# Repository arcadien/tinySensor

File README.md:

# TinySensor 

TinySensor aims to provide a customisable firmware and a hardware design for low-power environment sensors using wireless communication.

In the complete system, data is processed by a [Domoticz](https://domoticz.com/)/[RFlink](http://www.rflink.nl/blog2/) couple.
Data decoding is also tested using [RTL_433](https://github.com/merbanan/rtl_433) decoder.
Large part of the code, especially wireless encoders, are unit-tested.

| TinySensor v3.0 board (cuttable) | Mushroom casing | Wall box | tinyDecoders receiver |
|:---:|:---:|:---:|:---:|
|  |  |  |  |

*TinySensor v3.0 schematic (click to enlarge; [PDF with title block](hardware/tinysensor/tinysensor_schematic.pdf)). The board can be cut along the dotted line at x = 147 to drop the CR2032 area, as in the mushroom.*

## Supported MCUs
* ATTiny84a

## Supported sensors
* I2C sensors (eg. [Bosch BME/BMP280](https://www.bosch-sensortec.com/bst/products/all_products/bme280))
* Analog sensors (eg. [LM35](http://www.ti.com/lit/ds/symlink/lm35.pdf))
* OneWire sensors (eg. [Dallas DS18S20](https://datasheets.maximintegrated.com/en/ds/DS18S20.pdf))
* Luminosity sensor ([ROHM BH1750](https://www.mouser.com/datasheet/2/348/bh1750fvi-e-186247.pdf), I2C)

## Wireless technology
* "one pin" emitters. Tested with low-cost 433 MHz emitters.

## Wireless protocols
* Environment frame (temperature, humidity, pressure): Oregon Scientific v2.1 (class `OregonV3`) **or** Lacrosse WS7000, at most one per build. A build without either sends no environment frame.
* Luminosity: always a dedicated Lacrosse WS7000 frame (Oregon has no light frame), so `LACROSSE_ID` is required whenever the BH1750 is fitted.
* Battery level and analog input: optional X10 RFXmeter frames, not sent when the battery is low.

## Used libraries
Various libraries are used here, and some where tweaked to remove any Arduino dependencies, making the whole firmware more compact:
* Sparkfun [BME280 sensor library](https://github.com/sparkfun/SparkFun_BME280_Arduino_Library) with all SPI related code removed
* [Tiny I2C](https://github.com/arcadien/tiny-i2c.git) of [David Johnson-Davies](https://github.com/technoblogy)
* [Unity test harness](http://www.throwtheswitch.org/unity) from Throw The Switch, for all testing code
* DS18B20 library of [Jacek Wieczorek](https://github.com/Jacajack/avr-ds18b20)

## Useful documentation about low power AVR
* [AVR4013: picoPower Basics](http://www.microchip.com/downloads/en/AppNotes/doc8349.pdf)

## Development

The firmware is built with [PlatformIO](https://platformio.org/) and configured entirely at build time: each physical sensor is one PlatformIO environment (`S_02`…`S_05`, `robot`, `devmodule`, `SOLAR_TEST`, `mushroom`) whose `build_flags` select protocol, sensors and calibration. See [docs/environments.md](docs/environments.md) to calibrate or add a board.

```bash
pio test -d emitter -e native_debug        # encoder and library unit tests, on the host
pio test -d emitter -e native_cycle_oregon # one measurement cycle (runCycle) per build variant;
                                           # also native_cycle_oregon_vcc, _oregon_divider,
                                           # _lacrosse, _x10
pio run -d emitter -e S_02                 # firmware for one board
pio run -d emitter -e S_02 -t upload       # flash it
```

> **Flashing with a BME280 plugged in.** ISP and I2C share the ATtiny84A pins PA4 (SCK / SCL) and PA6 (MOSI / SDA). On **v3.0**, R9 and R10 (330 Ω) sit in series between the MCU and the sensor connectors J3/J14, so the programmer drives SCK and MOSI without the sensor holding them: the board should flash with the BME280 in place (not yet checked on a built board). On **v2.2 and earlier**, unplug the BME280 before flashing, otherwise flashing fails; always wire it through its JST connector, never solder it to the board.

CI runs the native tests (`native_debug` and every `native_cycle_*`), compile-fail checks for invalid flag combinations (`emitter/test/compile_fail/`), sensor-variant checks (`emitter/test/build_variants/`), `clang-format` and a build of every board (including `mushroom`).

* Architecture: [docs/architecture.md](docs/architecture.md)
* Step debugging over debugWIRE: [docs/debugging.md](docs/debugging.md)
* Requirements: see [Requirement-based development](#requirement-based-development) below

## Requirement-based development

This project follows requirement-based development (RBD): every behaviour of the firmware, the receiver and the boards is written down as a requirement before it is tested and coded. Each requirement, its tests and the commits that implement it can therefore be traced to each other.

The cycle for each change:

1. **Requirement.** The change is first written as a requirement with an ID such as `FUNC-OREGON-001` (category, domain, number), a status (`validated` or `draft`) and its dependencies.
2. **Tests.** Tests are written next. Each Unity test function carries the ID it verifies on the line above it: `// @req FUNC-OREGON-001`. Requirements that no host test can observe (AVR registers, wiring, bench measurements) say instead how they are verified: by inspection, by a build, or on the bench.
3. **Code.** The code then makes the tests pass. The linter (`clang-format` 18.1.8) and the full native test suite must pass before each commit.
4. **Commit.** Each commit names what it serves: `req(ID):`, `test(ID):`, `feat(ID):`, `tech(ID):`, `perf(ID):`, `ui(ID):`, `conf(ID):` or `arch(ID):`; `plan:` for workflow files; `hw:`, `docs:`, `fix:`, `chore:`, `style:` or `refactor:` outside the code cycle (`hw:` is added in `.rbd/config.yml`, `extra_commit_prefixes`). The rbd plugin's pre-push hook rejects any other prefix, and a code commit whose ID is missing or not `validated`.

`git log --grep FUNC-MAIN-001` and `grep -rn FUNC-MAIN-001 emitter/test` show where a requirement was written, tested and implemented.

| Document | Contents |
|---|---|
| [requirements/functional.md](requirements/functional.md) | `FUNC`: observable behaviour: radio frames, measurements, battery, receiver decoding, RFLink lines |
| [requirements/ui.md](requirements/ui.md) | `UI`: what the receiver OLED shows |
| [requirements/configuration.md](requirements/configuration.md) | `CONF`: build flags, PlatformIO environments, CI |
| [requirements/platform.md](requirements/platform.md) | `PLAT`: hardware use: pins, registers, timers, sleep, board pull-ups |
| [requirements/technical.md](requirements/technical.md) | `TECH`: classes, interfaces, memory layout, test doubles |
| [requirements/performance.md](requirements/performance.md) | `PERF`: none yet |
| [docs/architecture.md](docs/architecture.md) | Component diagram, dependency injection map, and a requirement → component traceability table |
| [audits/](audits/) | Audit and review reports. Each one starts with the commit it audited, so `git diff <hash>..HEAD` shows what changed since |
| [audits/exclusions.yml](audits/exclusions.yml) | Audit findings accepted on purpose, with their justification |
| [.rbd/config.yml](.rbd/config.yml) | ID format, test tag convention and linter command |

Non-technical requirements (`FUNC`, `UI`, `CONF`, `PLAT`) describe what can be observed, without class or function names. Those details live in `TECH`. Requirement IDs cited in these documents link to their heading. The workflow is driven by the [`rbd` Claude Code plugin](https://github.com/arcadien/claude-marketplace/tree/main/plugins/rbd) (`/rbd`, `/rbd-audit`, `/rbd-review`); see `CLAUDE.md`.

## Hardware and enclosure

* KiCad board (v3.0) in `hardware/tinysensor/`: [schematic (PDF)](hardware/tinysensor/tinysensor_schematic.pdf), regenerated with `kicad-cli sch export pdf -o hardware/tinysensor/tinysensor_schematic.pdf hardware/tinysensor/tinysensor.kicad_sch`; with its [backlog](hardware/tinysensor/BACKLOG.md) and a [rework guide for v2.2 boards](hardware/tinysensor/REWORK_v2.2.md).
* OpenSCAD enclosures (wall box, radiation shield, mushroom, receiver) in `enclosing/`, see [enclosing/README.md](enclosing/README.md).
* Header renders: `kicad-cli pcb render --rotate '-45,0,45' --quality high --width 1400 --height 800 --zoom 1.22 -o docs/img/tinysensor_v3_iso.png hardware/tinysensor/tinysensor.kicad_pcb` and, from `enclosing/receiver/`, `openscad --preview -D 'part="assembly"' --camera=0,0,0,55,0,25,0 --viewall --autocenter --projection=o --imgsize=1400,1000 -o ../../docs/img/receiver_iso.png receiver.scad`; from `enclosing/basic/`, `openscad --preview -D 'part="exploded"' --camera=0,0,0,55,0,25,0 --viewall --autocenter --projection=o --imgsize=1400,1000 -o ../../docs/img/wallbox_exploded_iso.png tinysensor_box.scad`. Schematic image: `kicad-cli sch export svg --exclude-drawing-sheet -o <dir> hardware/tinysensor/tinysensor.kicad_sch`, then a white background rectangle is added so it stays readable in dark mode.

## Hardware options

TinySensor can use combination of sensors, the limit comes from amount of flash memory on the ATTiny.

### DS18B20

OneWire sensor, cheap and efficient.

### BMP/BME 280 environment sensor
The [BMP280](https://www.bosch-sensortec.com/products/environmental-sensors/pressure-sensors/pressure-sensors-bmp280-1.html) and the [BME280](https://www.bosch-sensortec.com/products/environmental-sensors/humidity-sensors-bme280/) share the same library, but the BME provide humidity sensing, and thus use more memory.

### Analog sensor

Analog sensor can be used for [LM35](https://www.ti.com/lit/ds/symlink/lm35.pdf) temperature sensor, or [LDR](https://en.wikipedia.org/wiki/Photoresistor).

### LM35 temperature sensor

On v2.2 and v3.0 boards running from 2×AA/AAA, the LM35 can be powered by an off-board 5 V boost module switched on PB2 only during measurements (`USE_SWITCHED_5V`), see [VARIANTE_LM35.md](hardware/tinysensor/VARIANTE_LM35.md). The instructions below are for v2.1.

#### Without negative temperature support
A 0v ground reference is needed.
Solder pads *2* and *3* of **J4**, (rear side) as well **JP3**. 

#### With negative temperature support
In the case of a *-CAZ* version, temperature below 0 can be measured. 
To allow this, two 1N914 diodes must be placed to put the sensor reference below 0v. This setup is documented in the LM35 datasheet.
On TinySensor board v2.1 and up, this can be implemented by:
* solding **D2** and **D3** diodes
* solding **R4** with a value of 18k
* solding **JP3** to bypass C3 capacitor
* solding pads *1* and *2* of **J4** (rear side) to set ground reference.

#### Notes about swing

You can add a filter capacitor *C3* to avoid swing if the wire is long. In this case, do not solder *JP3*.
See datasheet for details.

### LDR
Use the right value for **R4** (should match the used LDR) and solder **JP3** and, on **JP4**, middle and *3* pads. This way, there will be no RC filter (no cap because of **J3**) and Vss analog reference thanks of **JP4**.

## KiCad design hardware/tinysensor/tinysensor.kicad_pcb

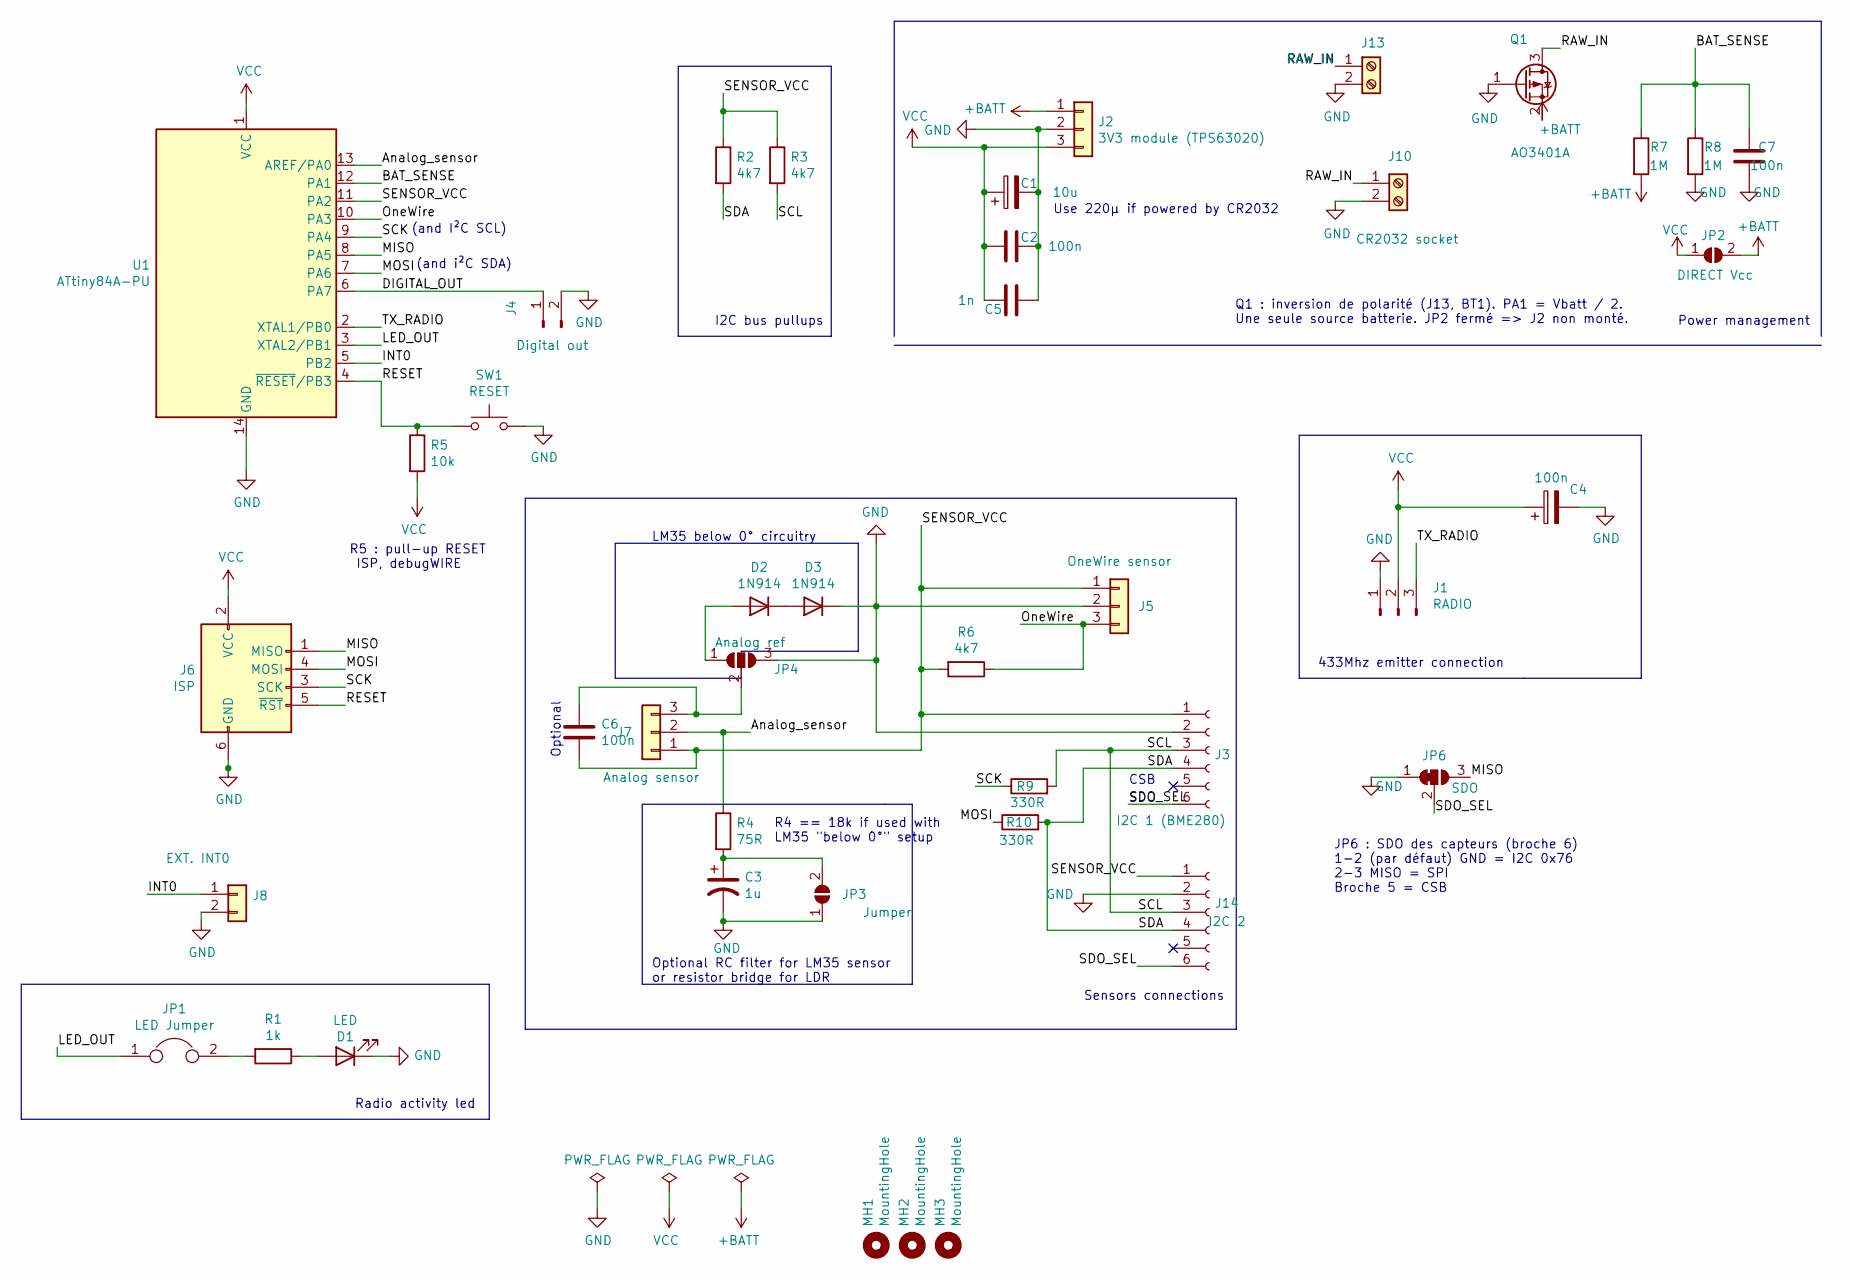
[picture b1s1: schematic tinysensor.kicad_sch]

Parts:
C1: 10u; CP_Radial_D6.3mm_P2.50mm
C2, C7: 100n; C_Rect_L7.0mm_W2.0mm_P5.00mm
C3: 1u; CP_Radial_D4.0mm_P1.50mm
C4, C6: 100n; C_Disc_D3.0mm_W1.6mm_P2.50mm
C5: 1n; C_Disc_D3.0mm_W1.6mm_P2.50mm
D1: LED; LED_D5.0mm
D2, D3: 1N914; D_DO-35_SOD27_P7.62mm_Horizontal
J1: RADIO; PinHeader_1x03_P2.54mm_Vertical
J2: 3V3 module (TPS63020); PinHeader_1x03_P2.54mm_Vertical
J3: I2C 1 (BME280); JST_EH_B6B-EH-A_1x06_P2.50mm_Vertical
J4: Digital out; PinHeader_1x02_P2.54mm_Vertical
J5: OneWire sensor; PinHeader_1x03_P2.54mm_Vertical
J6: ISP; ICSP_SOCKET_MINI_2x3
J7: Analog sensor; PinHeader_1x03_P2.54mm_Vertical
J8: EXT. INT0; PinHeader_1x02_P2.54mm_Vertical
J10: CR2032 socket; BatteryHolder_Keystone_1060_1x2032
J13: RAW IN; JST_XH_B2B-XH-A_1x02_P2.50mm_Vertical
J14: I2C 2; JST_EH_B6B-EH-A_1x06_P2.50mm_Vertical
JP1: LED Jumper; PinHeader_1x02_P2.54mm_Vertical
JP2: DIRECT Vcc; SolderJumper-2_P1.3mm_Open_TrianglePad1.0x1.5mm
JP3: Jumper; SolderJumper-2_P1.3mm_Open_TrianglePad1.0x1.5mm
JP4: Analog ref; SolderJumper-3_P1.3mm_Open_Pad1.0x1.5mm_NumberLabels
JP6: SDO; SolderJumper-3_P1.3mm_Open_Pad1.0x1.5mm_NumberLabels
MH1, MH2, MH3: MountingHole; MountingHole_3.2mm_M3
Q1: AO3401A; SOT-23
R1: 1k; R_Axial_DIN0204_L3.6mm_D1.6mm_P1.90mm_Vertical
R2, R3, R6: 4k7; R_Axial_DIN0204_L3.6mm_D1.6mm_P7.62mm_Horizontal
R4: 75R; R_Axial_DIN0204_L3.6mm_D1.6mm_P7.62mm_Horizontal
R5: 10k; R_Axial_DIN0204_L3.6mm_D1.6mm_P1.90mm_Vertical
R7, R8: 1M; R_Axial_DIN0204_L3.6mm_D1.6mm_P1.90mm_Vertical
R9, R10: 330R; R_Axial_DIN0204_L3.6mm_D1.6mm_P1.90mm_Vertical
SW1: RESET; SW_PUSH_6mm_H4.3mm
U1: ATtiny84A-PU; DIP-14_W7.62mm

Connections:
+BATT: J2.1, JP2.2 (B), Q1.2 (S), R7.2
/Analog_sensor: J7.2, R4.1, U1.13 (AREF/PA0)
/BAT_SENSE: C7.1, R7.1, R8.1, U1.12 (PA1)
/DIGITAL_OUT: J4.1, U1.6 (PA7)
/INT0: J8.1, U1.5 (PB2)
/LED_OUT: JP1.1, U1.3 (XTAL2/PB1)
/MISO: J6.1 (MISO), JP6.3 (B), U1.8 (PA5)
/MOSI: J6.4 (MOSI), R10.1, U1.7 (PA6)
/OneWire: J5.3, R6.1, U1.10 (PA3)
/RAW_IN: J10.1, J13.1, Q1.3 (D)
/RESET: J6.5 (~RST), R5.1, SW1.1, U1.4 (~RESET/PB3)
/SCK: J6.3 (SCK), R9.1, U1.9 (PA4)
/SCL: J3.3, J14.3, R3.2, R9.2
/SDA: J3.4, J14.4, R2.2, R10.2
/SDO_SEL: J3.6, J14.6, JP6.2 (C)
/SENSOR_VCC: C6.1, J3.1, J5.1, J7.1, J14.1, R2.1, R3.1, R6.2, U1.11 (PA2)
/TX_RADIO: J1.3, U1.2 (XTAL1/PB0)
GND: C1.2, C2.1, C3.2, C4.2, C5.2, C7.2, D1.1 (K), D3.1 (K), J1.1, J2.2, J3.2, J4.2, J5.2, J6.6 (GND), J8.2, J10.2, J13.2, J14.2, JP3.1 (A), JP4.3 (B), JP6.1 (A), Q1.1 (G), R8.2, SW1.2, U1.14 (GND)
unnamed: D1.2 (A), R1.1
unnamed: D2.2 (A), JP4.1 (A)
unnamed: D2.1 (K), D3.2 (A)
unnamed: C6.2, J7.3, JP4.2 (C)
unnamed: JP1.2, R1.2
unnamed: C3.1, JP3.2 (B), R4.2
VCC: C1.1, C2.2, C4.1, C5.1, J1.2, J2.3, J6.2 (VCC), JP2.1 (A), R5.2, U1.1 (VCC)

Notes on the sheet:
CSB
Radio activity led
Power management
Optional RC filter for LM35 sensor or resistor bridge for LDR
(and I²C SCL)
Q1 : inversion de polarité (J13, BT1). PA1 = Vbatt / 2. Une seule source batterie. JP2 fermé => J2 non monté.
SDO
Use 220µ if powered by CR2032
JP6 : SDO des capteurs (broche 6) 1-2 (par défaut) GND = I2C 0x76 2-3 MISO = SPI Broche 5 = CSB
R5 : pull-up RESET ISP, debugWIRE
Sensors connections
LM35 below 0° circuitry
I2C bus pullups
(and i²C SDA)
Optional
R4 == 18k if used with LM35 "below 0°" setup
433Mhz emitter connection

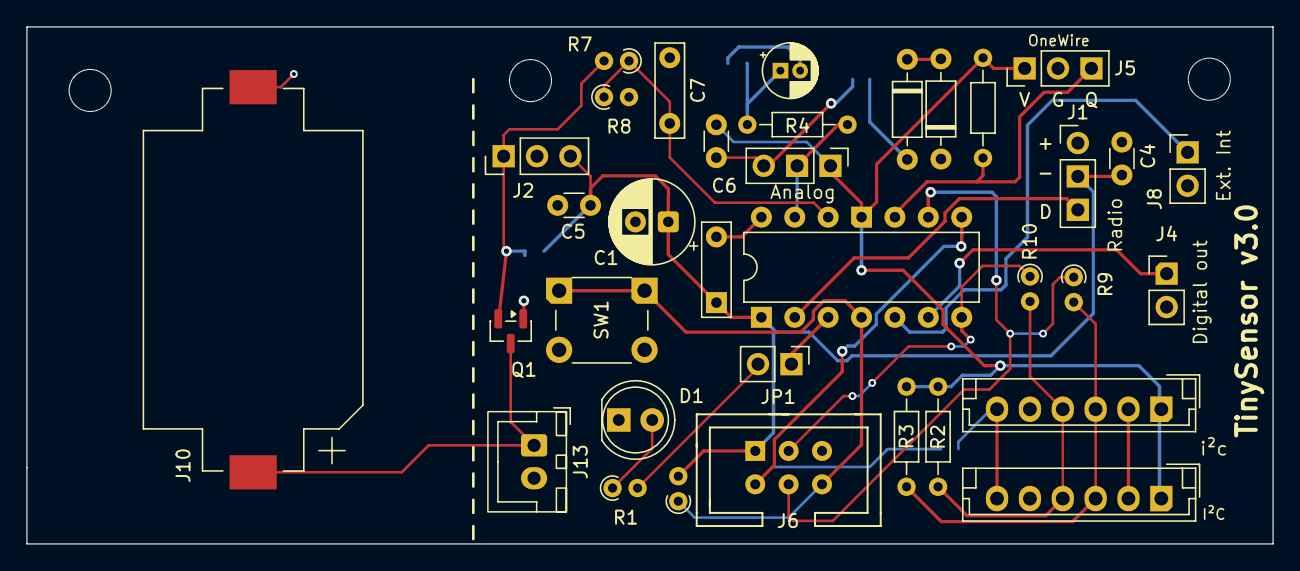
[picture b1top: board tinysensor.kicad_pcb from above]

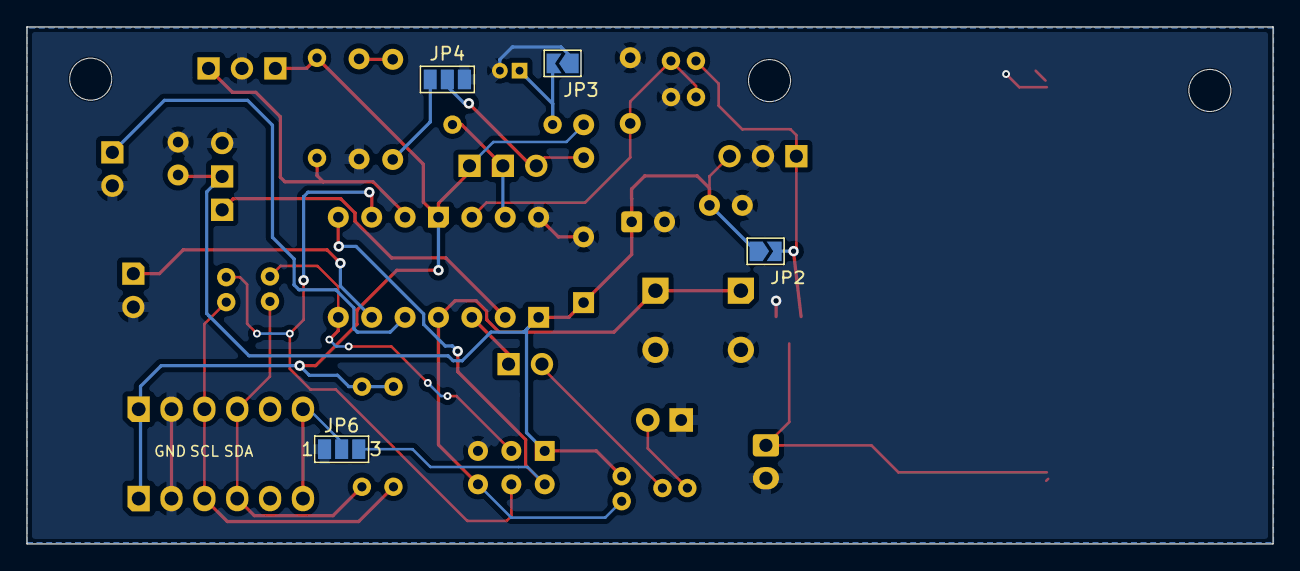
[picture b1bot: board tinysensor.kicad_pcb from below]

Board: 2 copper layers, 94.8 x 39.3 mm, 42 parts (4 on the bottom side), 25 nets.

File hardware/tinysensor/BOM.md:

# tinySensor board: bill of materials (v3.0)

Generated from the v3.0 schematic (`tinysensor.kicad_sch`, rev 3.0), grouped by value and footprint. No part is marked DNP: which connectors and modules to fit depends on the sensor unit, see [`WIRING.md`](WIRING.md) and [`docs/environments.md`](../../docs/environments.md). v2.2 boards: see [`REWORK_v2.2.md`](REWORK_v2.2.md).

Regenerate after a schematic change:

```bash
kicad-cli sch export bom --fields 'Reference,Value,Footprint,${QUANTITY}' \
  --labels 'Refs,Value,Footprint,Qty' --group-by 'Value,Footprint' --ref-range-delimiter '' \
  -o bom.csv tinysensor.kicad_sch
```

## Components

| Refs | Qty | Value | Package |
|---|:-:|---|---|
| U1 | 1 | ATtiny84A-PU | DIP-14 |
| Q1 | 1 | AO3401A (P-MOSFET) | SOT-23 |
| D1 | 1 | LED | 5 mm THT |
| D2, D3 | 2 | 1N914 | DO-35 |
| C1 | 1 | electrolytic, value per supply: 10 µF (2×AA/AAA, or 18650 through the TPS63020), 220 µF **low-leakage** (CR2032) | radial Ø6.3, 2.5 mm pitch |
| C3 | 1 | 1 µF electrolytic | radial Ø4, 1.5 mm pitch |
| C2 | 1 | 100 nF film (global decoupling) | 7 × 2 mm, 5 mm pitch |
| C7 | 1 | 100 nF film (PA1 battery divider; no tantalum: its leakage would bias the 500 kΩ divider) | 7 × 2 mm, 5 mm pitch |
| C4 | 1 | 100 nF ceramic (radio, next to J1) | disc Ø3, 2.5 mm pitch |
| C6 | 1 | 100 nF ceramic | disc Ø3, 2.5 mm pitch |
| C5 | 1 | 1 nF ceramic | disc Ø3, 2.5 mm pitch |
| R1 | 1 | 1 kΩ | axial DIN0204, vertical, 1.9 mm pitch |
| R2, R3, R6 | 3 | 4.7 kΩ | axial DIN0204, 7.62 mm pitch |
| R4 | 1 | 75 Ω | axial DIN0204, 7.62 mm pitch |
| R5 | 1 | 10 kΩ (RESET pull-up) | axial DIN0204, vertical, 1.9 mm pitch |
| R7, R8 | 2 | 1 MΩ (PA1 battery divider) | axial DIN0204, vertical, 1.9 mm pitch |
| R9, R10 | 2 | 330 Ω (SCL / SDA series, ISP isolation) | axial DIN0204, vertical, 1.9 mm pitch |
| SW1 | 1 | RESET push button | 6 mm THT, H 4.3 mm |

## Connectors and holders

| Refs | Qty | Function | Part |
|---|:-:|---|---|
| J1 | 1 | RADIO (433 MHz emitter) | 1×3 pin header, 2.54 mm |
| J2 | 1 | 3V3 module (TPS63020) | 1×3 pin header, 2.54 mm |
| J5 | 1 | OneWire sensor | 1×3 pin header, 2.54 mm |
| J7 | 1 | Analog sensor | 1×3 pin header, 2.54 mm |
| J4 | 1 | Digital out | 1×2 pin header, 2.54 mm |
| J8 | 1 | EXT. INT0 | 1×2 pin header, 2.54 mm |
| JP1 | 1 | LED jumper | 1×2 pin header, 2.54 mm + jumper cap |
| J3 | 1 | I2C 1 (BME280) | JST-EH 6-pin vertical, B6B-EH-A |
| J14 | 1 | I2C 2 | JST-EH 6-pin vertical, B6B-EH-A |
| J6 | 1 | ISP | 2×3 mini ICSP socket (project library) |
| J13 | 1 | RAW IN | JST-XH 2-pin vertical, B2B-XH-A |
| J10 | 1 | CR2032 socket | Keystone 1060 |

## No part to buy

| Refs | Function |
|---|---|
| JP2 | DIRECT Vcc solder jumper (2 pads, open) |
| JP3 | solder jumper (2 pads, open) |
| JP4 | Analog ref solder jumper (3 pads, open) |
| JP6 | BME280 SDO solder jumper (3 pads, open: bridge 1–2 for I2C at 0x76, the firmware address, or 2–3 for SPI; choose at assembly) |
| MH1–MH3 | M3 mounting holes |

## Off-board modules (not on the schematic)

Fitted per sensor unit, wiring in [`WIRING.md`](WIRING.md): 433 MHz OOK emitter on J1, BME280 or BMP280 breakout on J3, TPS63020 3.3 V buck-boost module on J2, DS18B20 on J5, LM35 variant on J7 ([`VARIANTE_LM35.md`](VARIANTE_LM35.md)), CR2032 in J10, or 2×AA/AAA or an 18650 (through a TP4056) on J13: the board has no 18650 holder.

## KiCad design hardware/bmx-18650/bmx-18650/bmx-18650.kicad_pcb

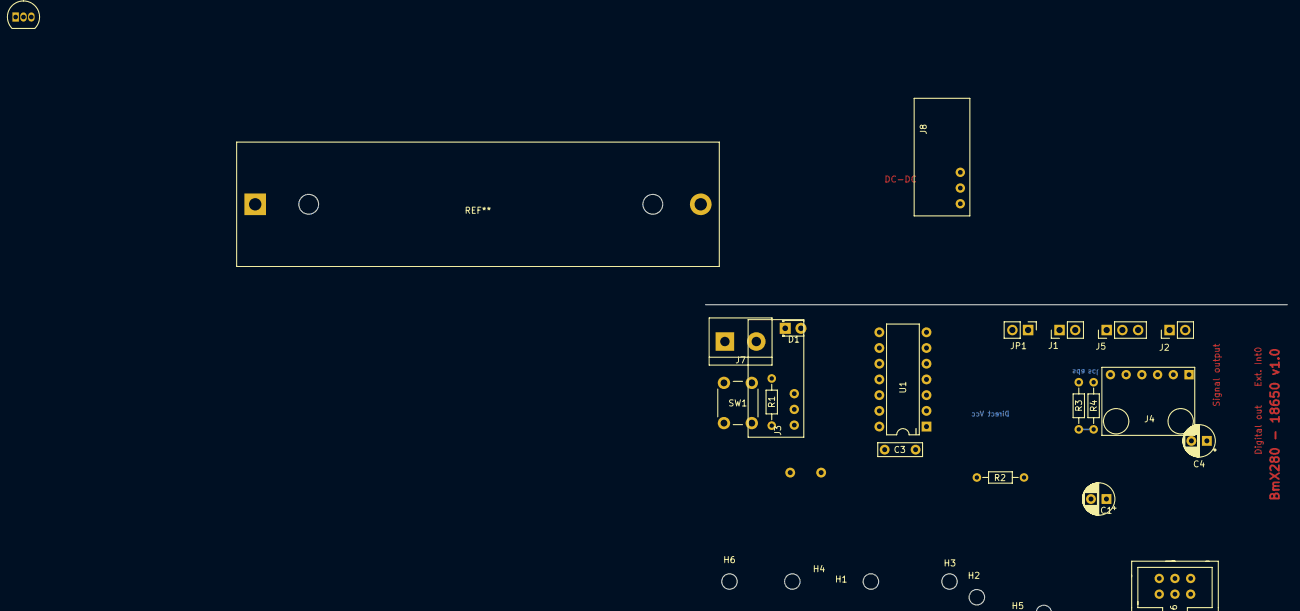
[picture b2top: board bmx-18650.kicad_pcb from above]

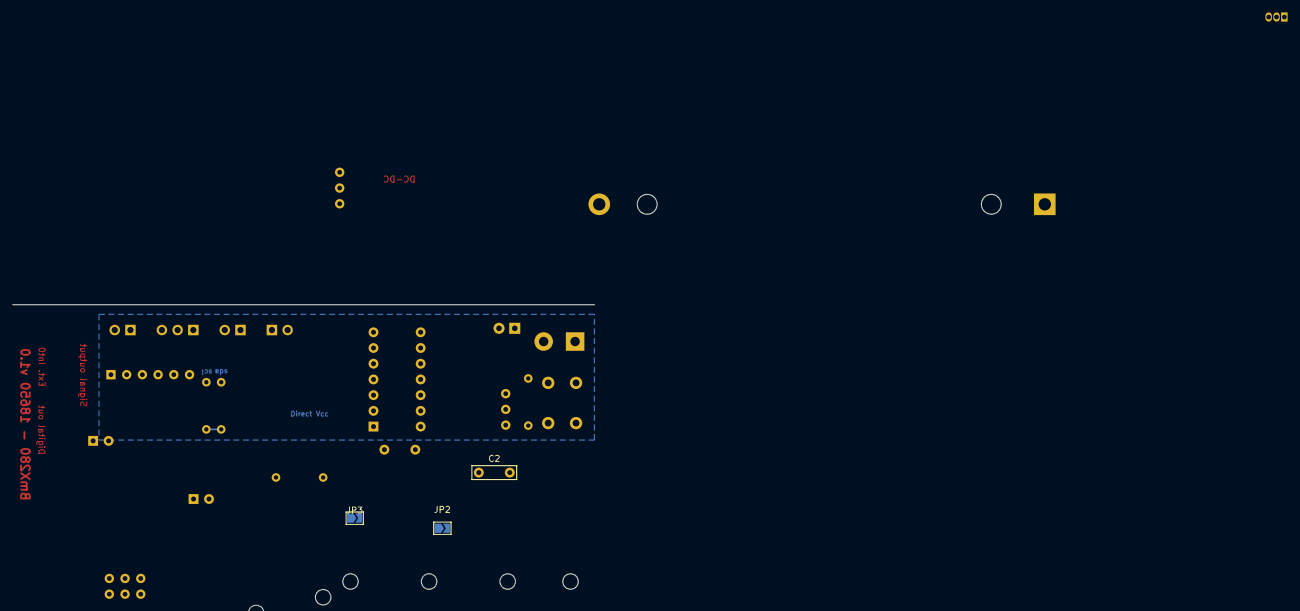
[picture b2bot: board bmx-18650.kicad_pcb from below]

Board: 2 copper layers, 29 parts (3 on the bottom side), 17 nets.

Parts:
C1, C4: 10u; CP_Radial_D5.0mm_P2.50mm
C2, C3: 100n; C_Rect_L7.0mm_W2.0mm_P5.00mm
D1: LED; LED_D1.8mm_W3.3mm_H2.4mm
H1, H2, H3, H4, H5, H6: MountingHole; MountingHole_2.5mm
J1: Ext. interrupt; PinHeader_1x02_P2.54mm_Vertical
J2: Digital out; PinHeader_1x02_P2.54mm_Vertical
J3: VCC charge pump; DC-DC_0.9v-3.3v_to_3.3v
J4: BMx280 socket; BMx280_breakout
J5: Radio emitter; PinHeader_1x03_P2.54mm_Vertical
J6: ISP; ICSP_SOCKET_MINI_2x3
J7: Terminal; TerminalBlock_bornier-2_P5.08mm
J8: RF charge pump; DC-DC_0.9v-3.3v_to_3.3v
JP1: LED Jumper; PinHeader_1x02_P2.54mm_Vertical
JP2, JP3: Bypass; SolderJumper-2_P1.3mm_Open_TrianglePad1.0x1.5mm
Q1: BS170; TO-92_Inline
R1, R3, R4: R; R_Axial_DIN0204_L3.6mm_D1.6mm_P7.62mm_Horizontal
R2: 10k; R_Axial_DIN0204_L3.6mm_D1.6mm_P7.62mm_Horizontal
SW1: SW_Push; SW_PUSH_6mm_H4.3mm
U1: ATtiny84A-PU; DIP-14_W7.62mm

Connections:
+BATT: J3.1, J7.1, J8.3, JP2.2 (B), JP3.1 (A), U1.12 (PA1)
/DIGITAL_OUT: J2.1, U1.6 (PA7)
/INT0: J1.1, U1.5 (PB2)
/LED_OUT: JP1.1, U1.3 (XTAL2/PB1)
/MISO: J6.1 (MISO), U1.8 (PA5)
/RESET: J6.5 (~RST), R2.1, SW1.1, U1.4 (~RESET/PB3)
/SCL: J4.3, J6.3 (SCK), R4.2, U1.9 (PA4)
/SDA: J4.4, J6.4 (MOSI), R3.2, U1.7 (PA6)
/SENSOR_VCC: J4.1, Q1.2 (G), R3.1, R4.1, U1.11 (PA2)
/TX_RADIO: J5.3, U1.2 (XTAL1/PB0)
GND: C1.2, C2.2, C3.1, C4.2, D1.2 (A), J1.2, J2.2, J3.2, J4.2, J4.6, J5.1, J6.6 (GND), J7.2, Q1.3 (S), SW1.2, U1.14 (GND)
unnamed: D1.1 (K), R1.1
unnamed: J8.2, Q1.1 (D)
unnamed: JP1.2, R1.2
unnamed: C2.1, U1.13 (AREF/PA0)
VCC: C1.1, C3.2, J3.3, J6.2 (VCC), JP2.1 (A), R2.2, U1.1 (VCC)
VDD: C4.1, J5.2, J8.1, JP3.2 (B)

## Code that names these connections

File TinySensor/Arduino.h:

/*
  pins_arduino.h - Pin definition functions for Arduino
  Part of Arduino - http://www.arduino.cc/

  Copyright (c) 2007 David A. Mellis
  Copyright (c) 2015~2020 Spence Konde

  This library is free software; you can redistribute it and/or
  modify it under the terms of the GNU Lesser General Public
  License as published by the Free Software Foundation; either
  version 2.1 of the License, or (at your option) any later version.

  This library is distributed in the hope that it will be useful,
  but WITHOUT ANY WARRANTY; without even the implied warranty of
  MERCHANTABILITY or FITNESS FOR A PARTICULAR PURPOSE.  See the GNU
  Lesser General Public License for more details.

  You should have received a copy of the GNU Lesser General
  Public License along with this library; if not, write to the
  Free Software Foundation, Inc., 59 Temple Place, Suite 330,
  Boston, MA  02111-1307  USA

  $Id: wiring.h 249 2007-02-03 16:52:51Z mellis $
*/

#ifndef Pins_Arduino_h
#define Pins_Arduino_h

#define ATTINYX4 1
#define __AVR_ATtinyX4__
#define USE_SOFTWARE_SPI 1

#include <avr/pgmspace.h>

#define NUM_DIGITAL_PINS            12
#define NUM_ANALOG_INPUTS           8

#define analogInputToDigitalPin(p)  (p)

#define digitalPinHasPWM(p)         ((p) == 5 || (p) == 6 || (p) == 7 || (p) == 8)

//This part has a USI, not an SPI module. Accordingly, there is no MISO/MOSI in hardware. There's a DI and a DO. When the chip is used as master, DI is used as MISO, DO is MOSI; the defines here specify the pins for master mode, as SPI master is much more commonly used in Arduino-land than SPI slave, and these defines are required for compatibility. Be aware of this when using the USI SPI fucntionality (and also, be aware that the MISO and MOSI markings on the pinout diagram in the datasheet are for ISP programming, where the chip is a slave. The pinout diagram included with this core attempts to clarify this)

#define ADC_TEMPERATURE 34

#define SS   3
#define MOSI 5
#define MISO 6
#define SCK  4


#define USI_DDR_PORT DDRA
#define USI_SCK_PORT DDRA
#define USCK_DD_PIN DDA4
#define DO_DD_PIN DDA5
#define DI_DD_PIN DDA6
#  define DDR_USI DDRA
#  define PORT_USI PORTA
#  define PIN_USI PINA
#  define PORT_USI_SDA PORTA6
#  define PORT_USI_SCL PORTA4
#  define PIN_USI_SDA PINA6
#  define PIN_USI_SCL PINA4
#  define USI_START_VECTOR USI_START_vect
#  define USI_OVERFLOW_VECTOR USI_OVF_vect
#  define DDR_USI_CL DDR_USI
#  define PORT_USI_CL PORT_USI
#  define PIN_USI_CL PIN_USI
#ifndef USI_START_COND_INT
#  define USI_START_COND_INT USISIF
#endif

static const uint8_t SDA = 6;
static const uint8_t SCL = 4;

//Ax constants should not be used for digitalRead/digitalWrite/analogWrite functions, only analogRead().
//#define ANALOG_PINS_ARE_ADC_NUMBERS 1
static const uint8_t A0 = 0x80 | 0;
static const uint8_t A1 = 0x80 | 1;
static const uint8_t A2 = 0x80 | 2;
static const uint8_t A3 = 0x80 | 3;
static const uint8_t A4 = 0x80 | 4;
static const uint8_t A5 = 0x80 | 5;
static const uint8_t A6 = 0x80 | 6;
static const uint8_t A7 = 0x80 | 7;

#define PIN_PA0  (0)
#define PIN_PA1  ( 1)
#define PIN_PA2  ( 2)
#define PIN_PA3  ( 3)
#define PIN_PA4  ( 4)
#define PIN_PA5  ( 5)
#define PIN_PA6  ( 6)
#define PIN_PA7  ( 7)
#define PIN_PB0  ( 10)
#define PIN_PB1  ( 9)
#define PIN_PB2  ( 8)
#define PIN_PB3  (11)  /* RESET */
#define LED_BUILTIN (8)

//Legacy
#define PIN_A0  (0)
#define PIN_A1  ( 1)
#define PIN_A2  ( 2)
#define PIN_A3  ( 3)
#define PIN_A4  ( 4)
#define PIN_A5  ( 5)
#define PIN_A6  ( 6)
#define PIN_A7  ( 7)
#define PIN_B0  ( 10)
#define PIN_B1  ( 9)
#define PIN_B2  ( 8)
#define PIN_B3  (11)  /* RESET */
#define LED_BUILTIN (8)

#define PINMAPPING_CW

//----------------------------------------------------------
//----------------------------------------------------------
//Core Configuration (used to be in core_build_options.h)



//Choosing not to initialise saves power and flash. 1 = initialise.
#define INITIALIZE_ANALOG_TO_DIGITAL_CONVERTER    1
#define INITIALIZE_SECONDARY_TIMERS               1
/*
  The old standby ... millis on Timer 0.
*/
#define TIMER_TO_USE_FOR_MILLIS                   0

/*
  Where to put the software serial? (Arduino Digital pin numbers)
*/
//WARNING, if using software, TX is on AIN0, RX is on AIN1. Comparator is favoured to use its interrupt for the RX pin.
#define USE_SOFTWARE_SERIAL           1
//Please define the port on which the analog comparator is found.
#define ANALOG_COMP_DDR               DDRA
#define ANALOG_COMP_PORT              PORTA
#define ANALOG_COMP_PIN               PINA
#define ANALOG_COMP_AIN0_BIT          1
#define ANALOG_COMP_AIN1_BIT          2


/*
  Analog reference bit masks.
*/
// VCC used as analog reference, disconnected from PA0 (AREF)
#define DEFAULT (0)
// External voltage reference at PA0 (AREF) pin, internal reference turned off
#define EXTERNAL (1)
// Internal 1.1V voltage reference
#define INTERNAL (2)
#define INTERNAL1V1 INTERNAL

//----------------------------------------------------------
//----------------------------------------------------------
//----------------------------------------------------------
//----------------------------------------------------------


// PCICR = Pin Change Interrupt Control Register
#define digitalPinToPCICR(p)    (((p) >= 0 && (p) <= 11) ? (&GIMSK) : ((uint8_t *)NULL))
#define digitalPinToPCICRbit(p) ( ((p) <= 7) ? PCIE0 : PCIE1 )
#define digitalPinToPCMSK(p)    ( ((p) <= 7) ? (&PCMSK0) : (((p) <= 10) ? (&PCMSK1) : ((uint8_t *)NULL)) )
#define digitalPinToPCMSKbit(p) ( ((p) <= 7) ? (p) : (10 - (p)) )

#define digitalPinToInterrupt(p)  ((p) == 8 ? 0 : NOT_AN_INTERRUPT)
#ifdef ARDUINO_MAIN
#warning "This is the CLOCKWISE pin mapping - make sure you're using the pinout diagram with the pins in clockwise order"
// ATMEL ATTINY84 / ARDUINO
//
//                           +-\/-+
//                     VCC  1|    |14  GND
//            (D  10)  PB0  2|    |13  PA0  (D  0)        AREF
//             (D  9)  PB1  3|    |12  PA1  (D  1)
//             (D 11)  PB3  4|    |11  PA2  (D  2)
//  PWM  INT0  (D  8)  PB2  5|    |10  PA3  (D  3)
//  PWM        (D  7)  PA7  6|    |9   PA4  (D  4)
//  PWM        (D  6)  PA6  7|    |8   PA5  (D  5)        PWM
//                           +----+
const uint16_t PROGMEM port_to_mode_PGM[] =
{
  NOT_A_PORT,
  (uint16_t)&DDRA,
  (uint16_t)&DDRB,
};

const uint16_t PROGMEM port_to_output_PGM[] =
{
  NOT_A_PORT,
  (uint16_t)&PORTA,
  (uint16_t)&PORTB,
};

const uint16_t PROGMEM port_to_input_PGM[] =
{
  NOT_A_PORT,
  (uint16_t)&PINA,
  (uint16_t)&PINB,
};

const uint8_t PROGMEM digital_pin_to_port_PGM[] =
{
  PA, /* 0 */
  PA,
  PA,
  PA,
  PA,
  PA,
  PA,
  PA,
  PB, /* 8 */
  PB,
  PB,
  PB, /* 11 */
};



const uint8_t PROGMEM digital_pin_to_bit_mask_PGM[] =
{
  _BV(0), /* port A */
  _BV(1),
  _BV(2),
  _BV(3),
  _BV(4),
  _BV(5),
  _BV(6),
  _BV(7),
  _BV(2), /* port B */
  _BV(1),
  _BV(0),
  _BV(3),
};

const uint8_t PROGMEM digital_pin_to_timer_PGM[] =
{
  NOT_ON_TIMER,
  NOT_ON_TIMER,
  NOT_ON_TIMER,
  NOT_ON_TIMER,
  NOT_ON_TIMER,
  TIMER1B, /* OC1B */
  TIMER1A, /* OC1A */
  TIMER0B, /* OC0B */
  TIMER0A, /* OC0A */
  NOT_ON_TIMER,
  NOT_ON_TIMER,
  NOT_ON_TIMER,
};

#endif

#endif




//Old code, just here for temporary backup until I decide it is not needed.
/*
//WARNING, if using software, RX must be on a pin which has a Pin change interrupt <= 7 (e.g. PCINT6, or PCINT1, but not PCINT8)
#define USE_SOFTWARE_SERIAL             1
//These are set to match Optiboot pins.
#define SOFTWARE_SERIAL_PORT            PORTA
#define SOFTWARE_SERIAL_TX              9
#define SOFTWARE_SERIAL_PIN             PINA
#define SOFTWARE_SERIAL_RX              8*/

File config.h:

/*
 * config.h
 *
 * Created: 19/11/2018 22:14:40
 *  Author: aurelien
 */

#ifndef CONFIG_H_
#define CONFIG_H_

#include <inttypes.h>

// sleep 32s between each sample and
// emission
#define SLEEP_TIME_IN_SECONDS (8 * 4)

/*
 * 1-wire interface is on PA3
 * Power for radio is on PA2 (sensor_vcc)
 * LED pin is PB1
 * PWM pin is PA7
 * SDA pin is PA6
 * SCL pin is PA4
 * MISO pin is PA5
 * TX radio pin is PB0
 * BAT sensor pin is PA1
 * analog sensor pin is PA0
 */
#define LED_PIN PB1
#define PWM_PIN PA7
#define TX_RADIO_PIN PB0
#define RADIO_POWER_PIN PA2
#define BAT_SENSOR_PIN PA1

// Sensors
#define USE_BMP280
//#define USE_BME280
//#define USE_DS18B20 
// Protocols
#define USE_OREGON 1

// 0x5A, 0x5D pressure, temp, hygro
// 0xEA, 0x4C temp only
const uint8_t OREGON_TYPE[] = {0xEA, 0x4C};
const uint8_t OREGON_ID = 0xCB;

/*
 * MODE_0 0 // Temperature only [THN132N]
 * MODE_1 1 // Temperature + Humidity [THGR2228N]
 * MODE_2 2 // Temperature + Humidity + Baro() [BTHR918N]
 */
#define OREGON_MODE MODE_0

#endif /* CONFIG_H_ */
